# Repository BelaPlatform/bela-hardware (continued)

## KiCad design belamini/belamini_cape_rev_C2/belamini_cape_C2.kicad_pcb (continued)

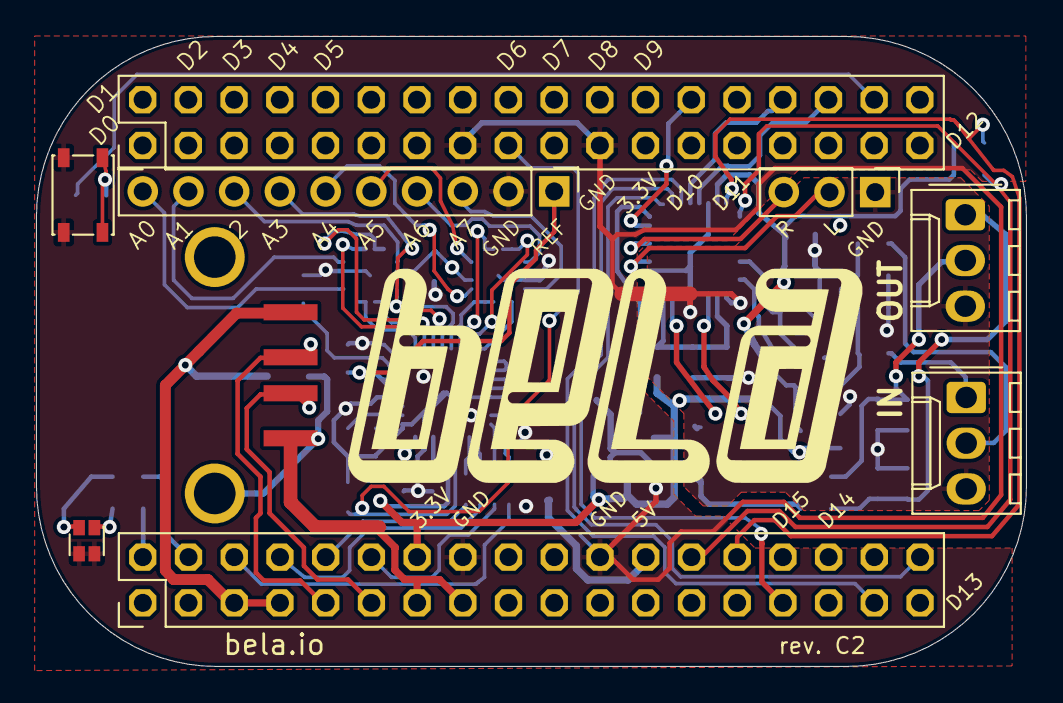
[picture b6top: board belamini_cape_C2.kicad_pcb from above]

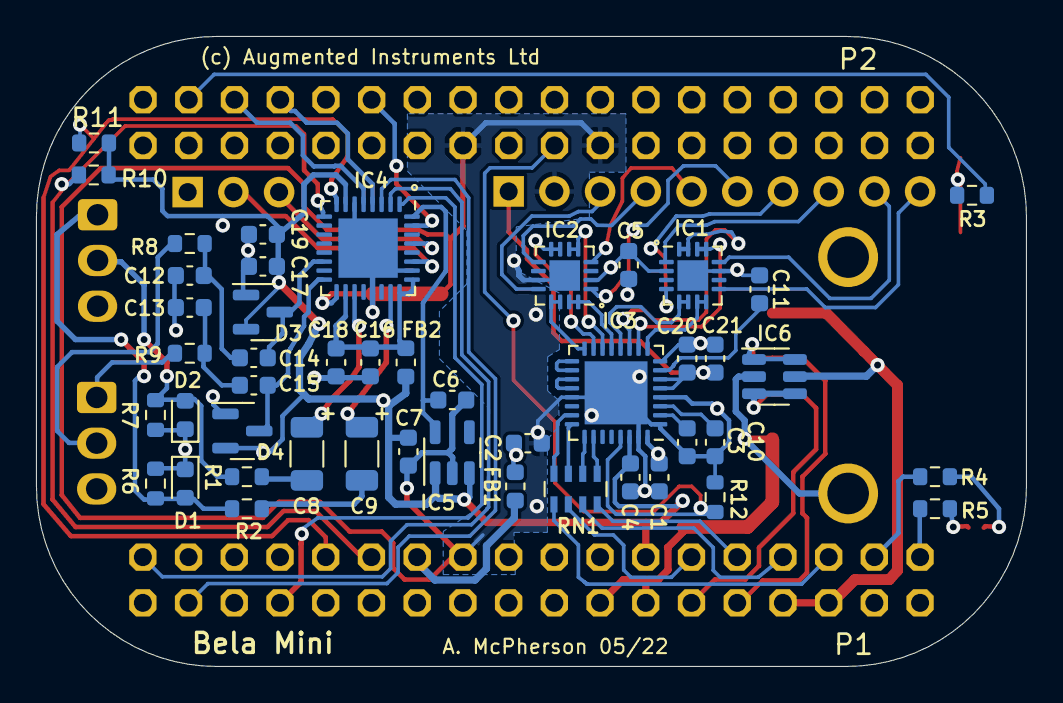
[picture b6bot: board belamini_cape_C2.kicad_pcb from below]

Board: 4 copper layers, 55.0 x 35.0 mm, 55 parts (46 on the bottom side), 69 nets.

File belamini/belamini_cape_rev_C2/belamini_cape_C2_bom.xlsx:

Name | Quantity | Value | Side | Package | Description | Farnell # | Mouser # | Datasheet / Notes
 |  |  |  |  |  |  | 810-C1608X5R1A106M
C2, C18, C19, C20, C21 | 5 | 10uF | bottom | “0603” | Capacitor ceramic 0603 | 2309028
C3, C7, C10, C11, C14, C15 | 6 | 1uF | bottom | “0603” | Capacitor ceramic 0603 | 2496916 | 77-VJ0603V105MXQPBC
C1, C4, C5, C6, C16, C17 | 6 | 0.1uF | bottom | “0603” | Capacitor ceramic 0603 | 1709957 | 80-C0603C104K5R
C12, C13 | 2 | 47pF | bottom | "0603" | Capacitor ceramic 0603 | 1759062 | 77-VJ0603A470JXACBC
C8, C9 | 2 | 47uF | bottom | "1206" | Capacitor electrolytic 1206 | 2353044 | 647-F930J476MAA
D1, D2 | 2 | TE Connectivity PESD0603-240 | bottom | "0603" | ESD suppressor 24V |  | 650-PESD0603-240
D3, D4 | 2 | BAS70-04 | bottom | SOT23-3 | Dual Schottky diode |  | 863-BAS70-04LT1G |  |  |  |  |  | D3, D4
D5 | 1 | Lite-On LTST-C195TBJRKT | top | “0606” | blue/red LED |  | 859-LTST-C195TBJRKT | Important: check pinout of any generic equivalent part. Dot indicates the negat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
FB1, FB2 | 4 | Ferrite bead | bottom | “0603” | Ferrite bead 0603 | 1781090 | 810-MPZ1608S121A
IC1, IC2 | 2 | TSV524 | bottom | QFN-16 | Quad op-amp |  | 511-TSV524IQ4T
IC3 | 1 | ADS8168IRHBT | bottom | QFN-32 | 16-bit ADC |  | 595-ADS8168IRHBT | Other parts in ADS816x series may also work.
IC4 | 1 | TLV320AIC3104 | bottom | QFN-32 | Audio codec |  | 595-TLV320C3104IRHBR
IC5 | 1 | MIC5317-1.8Y | bottom | SOT23-5 | 1.8V regulator |  | 998-MIC5317-1.8YM5TR
IC6 | 1 | USBLC6-2SC6 | bottom | SOT23-6 | ESD suppressor for USB |  | 511-USBLC6-2SC6
J1 | 1 | 10-pin socket | top | Through Hole | 10-pin socket |  | 992-10FX1-254MM
J2 | 1 | 3-pin header | top | Through Hole | 3-pin socket |  | 855-M20-7820346
J3, J4 | 2 | Molex 3-pin | top | Through Hole | 3-pin Molex KK series connector |  | 538-22-23-2031
J5 | 1 | Amphenol 87583-3010RPALF | top | Solder Pad | USB A socket, solder pad | 1314363 | 649-87583-3010RPALF
P1, P2 | 2 | 36-pin header | top | Through Hole | 2x18 2.54mm stacking headers (10mm male pins on bottom, female sockets on top). |  |  | Important: use 10mm pin length rather than 12.5mm used on previous Bela builds
R1, R2 | 2 | 15 ohm | bottom | “0603” | Resistor 0603
R3 | 1 | 100 ohm | bottom | “0603” | Resistor 0603
R4, R5 | 2 | 560 ohm | bottom | “0603” | Resistor 0603
R6, R7 | 2 | 3.3k ohm | bottom | “0603” | Resistor 0603
R8, R9 | 2 | 220 ohm | bottom | “0603” | Resistor 0603
R10, R11, R12 | 3 | 10k ohm | bottom | “0603” | Resistor 0603
RN1 | 1 | 22 ohm 4x network | bottom | “0603” | Resistor network 4x0603 | 2060086
S1 | 1 | C&K Components PTS810 SJG 250 SMTR LFS | top | SMD | Micro tactile switch |  | 611-PTS810SJG250SMTR
Total | 57
BOM rev. C2

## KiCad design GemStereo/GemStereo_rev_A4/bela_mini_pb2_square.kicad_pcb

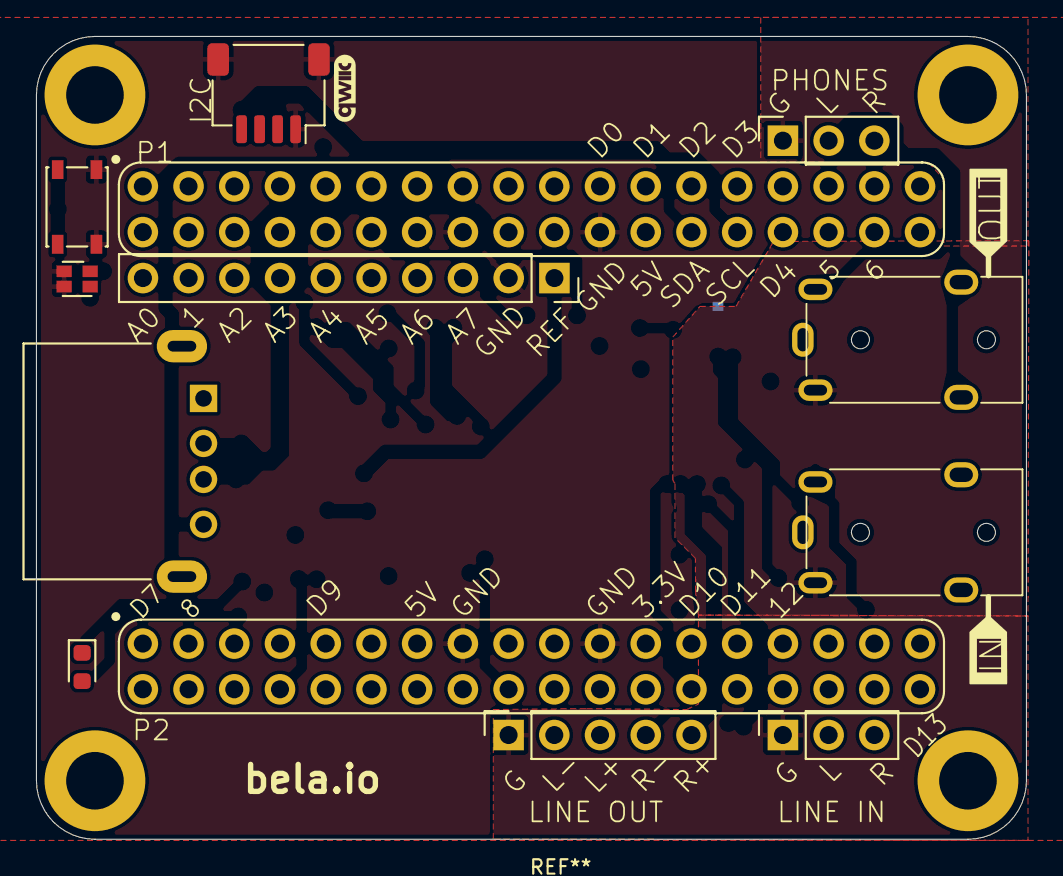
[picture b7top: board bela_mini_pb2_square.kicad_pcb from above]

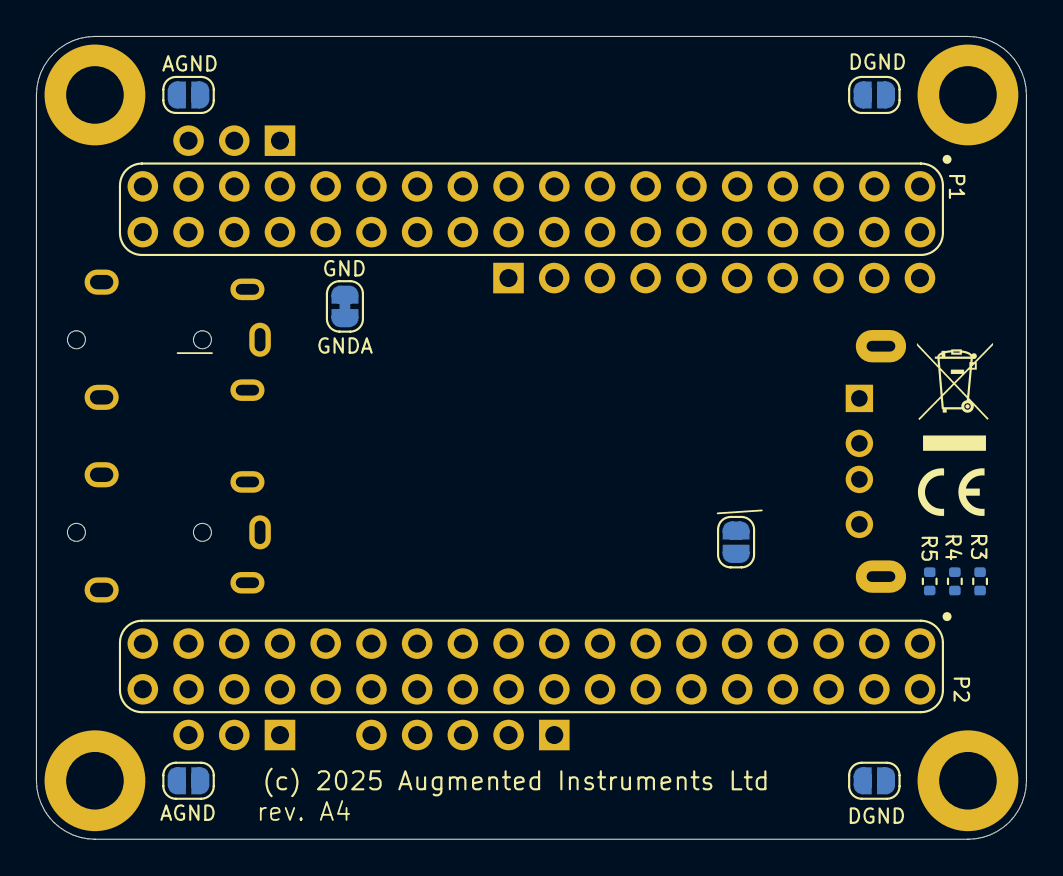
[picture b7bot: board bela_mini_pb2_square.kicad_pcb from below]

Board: 4 copper layers, 55.0 x 44.6 mm, 26 parts (11 on the bottom side), 24 nets, no tracks yet.

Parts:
D1: LTST-C195TBJRKT; LED_LiteOn_LTST-C19HE1WT
D6: LED; LED_0603_1608Metric
G2: WEEE-Logo; WEEE-Logo_4.2x6mm_SilkScreen
H1, H2, H3, H4: MountingHole; MountingHole_3.2mm_M3_DIN965_Pad
J1, J2: Conn_01x03; PinSocket_1x03_P2.54mm_Vertical
J3: Conn_01x10; PinSocket_1x10_P2.54mm_Vertical
J5: USB_A; USB_A_GCT_USB1125
J6: Conn_01x04_MountingPin; qwiic_horizontal_SMD
J7, J8: AudioJack4; Jack_3.5mm_LumbergSubstitute
J9: Conn_01x05; PinSocket_1x05_P2.54mm_Vertical
JP1, JP2, JP3, JP4, JP5: SolderJumper_2_Open; SolderJumper-2_P1.3mm_Open_RoundedPad1.0x1.5mm
NT1: NetTie_2; SolderJumper-2_P1.3mm_Bridged_RoundedPad1.0x1.5mm
R3: 100; R_0402_1005Metric
R4, R5: 560; R_0402_1005Metric
S1: PTS810; SW_SPST_PTS810
U1: PocketBeagle2; PB2

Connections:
+3V3: J6.2, JP2.1 (A), U1.P1.14 (3.3V), U1.P2.23 (3.3V)
+5V: U1.P1.24 (VOUT), U1.P2.13 (VOUT)
/HPL: J2.2, J8.T
/HPR: J2.3, J8.R1
/I2C2.SCL: J6.4, U1.P1.28 (I2C2.SCL)
/I2C2.SDA: J6.3, U1.P1.26 (I2C2.SDA)
/INL: J1.2, J7.T
/INR: J1.3, J7.R1
/LED_INDICATOR_A: R4.1, U1.P2.2 (PRU1.0)
/LED_INDICATOR_B: R5.2, U1.P2.4 (PRU1.1)
/ON_OFF_BUTTON: R3.2, U1.P2.6 (PRU1.2)
/USBGND: J5.4 (GND), J5.5 (Shield), U1.P1.15 (GND)
/USB_DN: J5.2 (D-), U1.P1.9 (USB1.D-)
/USB_DP: J5.3 (D+), U1.P1.11 (USB1.D+)
/USB_VBUS: J5.1 (VBUS), U1.P1.5 (USB1.VBUS), U1.P1.7 (VIN.USB)
GND: D1.3 (K1), D1.4 (K2), J3.2, J6.1, J6.MP (MountPin), JP1.2 (B), JP4.2 (B), NT1.2, S1.1, U1.P1.16 (GND), U1.P1.22 (GND), U1.P2.15 (GND), U1.P2.21 (GND)
GNDA: J1.1, J2.1, J7.R2, J8.R2, J9.1, JP3.2 (B), JP5.2 (B), NT1.1
unnamed: D1.1 (A1), R5.1
unnamed: D1.2 (A2), R4.2
unnamed: H1.1, JP1.1 (A)
unnamed: H2.1, JP3.1 (A)
unnamed: H3.1, JP4.1 (A)
unnamed: H4.1, JP5.1 (A)
unnamed: R3.1, S1.2

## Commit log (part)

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2016-07-22 Added Bela cape, multiplexer capelet and supporting EAGLE files
2016-07-26 Added Audio Expander Capelet design files (rev A2)
2016-10-10 Added pdf renders of the schematics
2016-12-08 Added pdf rendering of the board file for the cape
2017-05-18 Added frequency response for audio expander capelet
2017-09-01 Updated Bela cape to rev B2; closes #1, #2, #4
2017-09-25 Added PocketBela cape by @apmcpherson
2017-12-11 Added pdf rendering of the board and schematics for cape revB2
2018-01-23 Added rev. B mini cape files
2018-02-04 Updated Bela mini BOM to fix missing resistors and socket
2018-03-08 Added ESD suppressor IC6 to USB port; grounded USB ID pin; added labels and updated BOM
2018-03-11 Added Gerbers for mini cape rev. B2, updated BOM, and created an EAGLE CAM job for the mini cape.
2018-03-19 belamini test jig
2018-03-20 belamini test jig attempt 2
2018-03-20 Removed unneeded files
2018-03-20 Line out is DC-coupled, so no need for external components
2018-06-08 ignoring Eagle's temp files
2018-12-07 renamed belamini folder and added pdf schematics and board of belamini
2020-07-04 Added rev. B3 of the Bela cape
2020-07-04 Rev. B3 of the Bela Mini cape adds resistors R6 and R7 to reduce the noise when the audio output is driving a DI box and the codec is not active.
2020-07-04 Modified readme to also include Kicad as cad software used for the designs
2020-07-04 Updated with licensing details
2020-07-04 Added KiCad symbol and footprint for Bela Mini
2020-07-04 Add rev. B4 of Bela cape, moving some traces on the bottom layer for improved manufacturing reliability.
2020-11-30 Add manufacturing files for Bela Mini rev. B4
2020-11-30 Bela Mini rev. B4: addresses #7, #8, #10, #11
2021-11-09 Update README.md
    https://forum.kicad.info/t/warning-avoid-all-links-to-kicad-pcb-org-use-kicad-org/31521
2021-11-09 Update README.md (#13)
    https://forum.kicad.info/t/warning-avoid-all-links-to-kicad-pcb-org-use-kicad-org/31521
2022-01-11 MiniMulti rev. A2 designs
2022-03-24 Added dimensions pdf for Bela cape.
2022-03-24 Added dimensions pdf for bela mini starter kit
2022-08-16 First draft of mini rev. C1, with new ADC and move to KiCad
2022-08-16 Added Bela Mini rev. C2, fixing a couple issues in C1
2022-08-16 Mini rev. C1: change IC3 on the BOM
2022-08-16 Add logo to Mini rev. C1, clean up schematic and add production files
2023-01-05 typo
2023-03-12 ignore backup files since we have git history, right?
2023-03-12 updated gitignore
2023-03-12 Updates to Bela cape C1, adding 3-pin connectors for raw analog out
    (cherry picked from commit eb88a9ebe73bf9c3f735ce6d0fd609408781e91a)
2023-03-12 Bela cape rev. C1 - design in progress
    (cherry picked from commit 96cf0ad517c32be44510b9f78b20fff38d2effcd)
2023-03-12 More C1 cape routing
    (cherry picked from commit db7d999e21b46c22925661ce0002776775f31ffd)
2023-03-12 Further routing on C1 cape
    (cherry picked from commit 232a25b01e013bf194cdc3a343766aa7b43870aa)
2023-03-12 First complete routing of C1 cape
    (cherry picked from commit 8c5092941a0b3ec42f55098733fd0108b2086674)
2023-03-12 C1 cape: clean up bottom silkscreen
    (cherry picked from commit 7c02b20f8f7a862246e5856b6fa8015b8ad6464b)
2023-03-12 Ignored (and discarded) kicad_prl files
    (cherry picked from commit b86f11e499d9a74027bf78e27e7b6f224d72f43f)
2023-03-12 Further C1 cape updates
    (cherry picked from commit 4c76e949636c5b1483c5ffba2ecc0f217292ab87)
2023-03-12 Bela cape C1: renumber components
    (cherry picked from commit 6ebfe9c44bb7559ffb4c9dbd092e49803523e6a1)
2023-03-12 First complete iteration of C1 cape layout
    (cherry picked from commit 0ee733c70b42f416809330055e007cefcdb105fa)
2023-03-12 changed board setup to include Bela cape colors, added 3dmodels for button and LED
    (cherry picked from commit fac969fb978c1abdbab94b44e3f4f5c1f13dcd93)
2023-03-12 Bela cape rev. C2
    (cherry picked from commit 085b3700cd1d9a25c77092a8b59a7c103f45927b)
2023-03-12 added missing 3dmodels for IC packages
    (cherry picked from commit 85806714f40e67aeb9d357d275771518137d9dca)
2023-03-12 Bodge board to fix an error on C2 capes
    (cherry picked from commit f68d599e191e370001d2d3aca018898c47946fe5)
2023-03-12 added NC flags to pins in Cape rev C2 to reduce ERC errors
    (cherry picked from commit 3da46686a35f9c5723f0363d277e8b6402ee2362)
2023-03-12 Changed panel to 6x7 with 3mm gap and 0.35mm distance to v-scoring.
    (cherry picked from commit ada2b1bb84732b3d844c1010702f27f798faad04)
2023-03-12 A few edits to C2 cape
    (cherry picked from commit 42570a0d57f5cd6d8ff56c36d77f2d0b211cc62f)
2023-03-12 Edit to C2 cape fix
    (cherry picked from commit b205a86061b78b52253ac275e5139adb0c372d47)
2023-03-12 Added kikit configuration file for posterity
    (cherry picked from commit 343436336812e16e1a1f06097494a23a2ce2b96c)
2023-03-12 Added panel and gerbers for fix board
    (cherry picked from commit a0c660b927de1cd35729b3ca257c25d34b100ddd)
2023-03-12 Cape rev C3 first draft
    (cherry picked from commit 13e247bb11a8ca90d5cea0bc35d4eceea4ae0f39)
2023-03-12 Reduce size of connector holes on C3 cape
    (cherry picked from commit 2d14684a246b05362e5486009cff8026d4af1add)
2023-03-12 Add analog out connection to P8.15 for future BBAI64 support
2024-02-27 removed sym-lib-table with a reference to an unused and obsolete local library
2024-02-27 added missing footprints and symbols, updated their use in the schematic, referenced them as local path in schematic and layout
2024-12-06 Adding bela mini add-on footprint
2025-04-11 Added belamini system 3dmodel, updated footprint
2025-04-16 added audio I/O to belamini symbol/fp, made footprint DRC error-free
2026-02-06 Added Bela-Gem symbols, footprints, 3d
2026-02-06 added GemStereo and GemMulti A4
2026-02-07 adding spacers, screw, PB2 models
2026-02-09 removed logos
2026-02-13 Renaming Gem KiCad files
2026-03-19 bela-kicad-library updated to 6883fdbc30aeec6c245b02afa28c44308841621c
2026-05-04 adding VIN (P1.1) to standard Gem Stereo/Multi Symbols/
2026-05-22 added GemMulti wing_top and wing_bottom from a7cc44841b7c9501ee3d858750621b35dcaec8b8
